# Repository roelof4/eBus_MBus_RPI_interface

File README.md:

# eBus_MBus_RPI_interface
Raspberry PI interface for eBus and M-Bus.

The interface combines a slave eBus interface and a master Mbus interface. This combination
is often present in heating systems such as gas boilers and heatpumps. For example, Vaillant
uses eBus to read and control.
The Mbus master is ideal to read heat meters, water meters and other sensors.
This interface provides power to the sensors and is thus classified as the master.
For safety purposes the eBus interface is fully galvanically shielded using optocouplers.

Both interfaces can be linked to serial (UART) ports on the Raspberry Pi. Version 4 and beyond
provide more than two UARTS and the user can select which one is used for either interface.
Older Raspberries can typically only use one UART. For these case the user can use serial to usb
cables using a separate 4-pin connector. Two are provided such that in principle the board
can be used standalone provided a 5V powersupply is present. When mounted as a HAT on the
Raspberry the 5V supply provided through the GPIO connector is used.

The interface also features a ONE WIRE sensor screw terminal which can act as a multiple temperature
sensor input (or whatever other ONE WIRE device available).

Note: the I2C EEPROM is optional and used for a system with automatic recognition.

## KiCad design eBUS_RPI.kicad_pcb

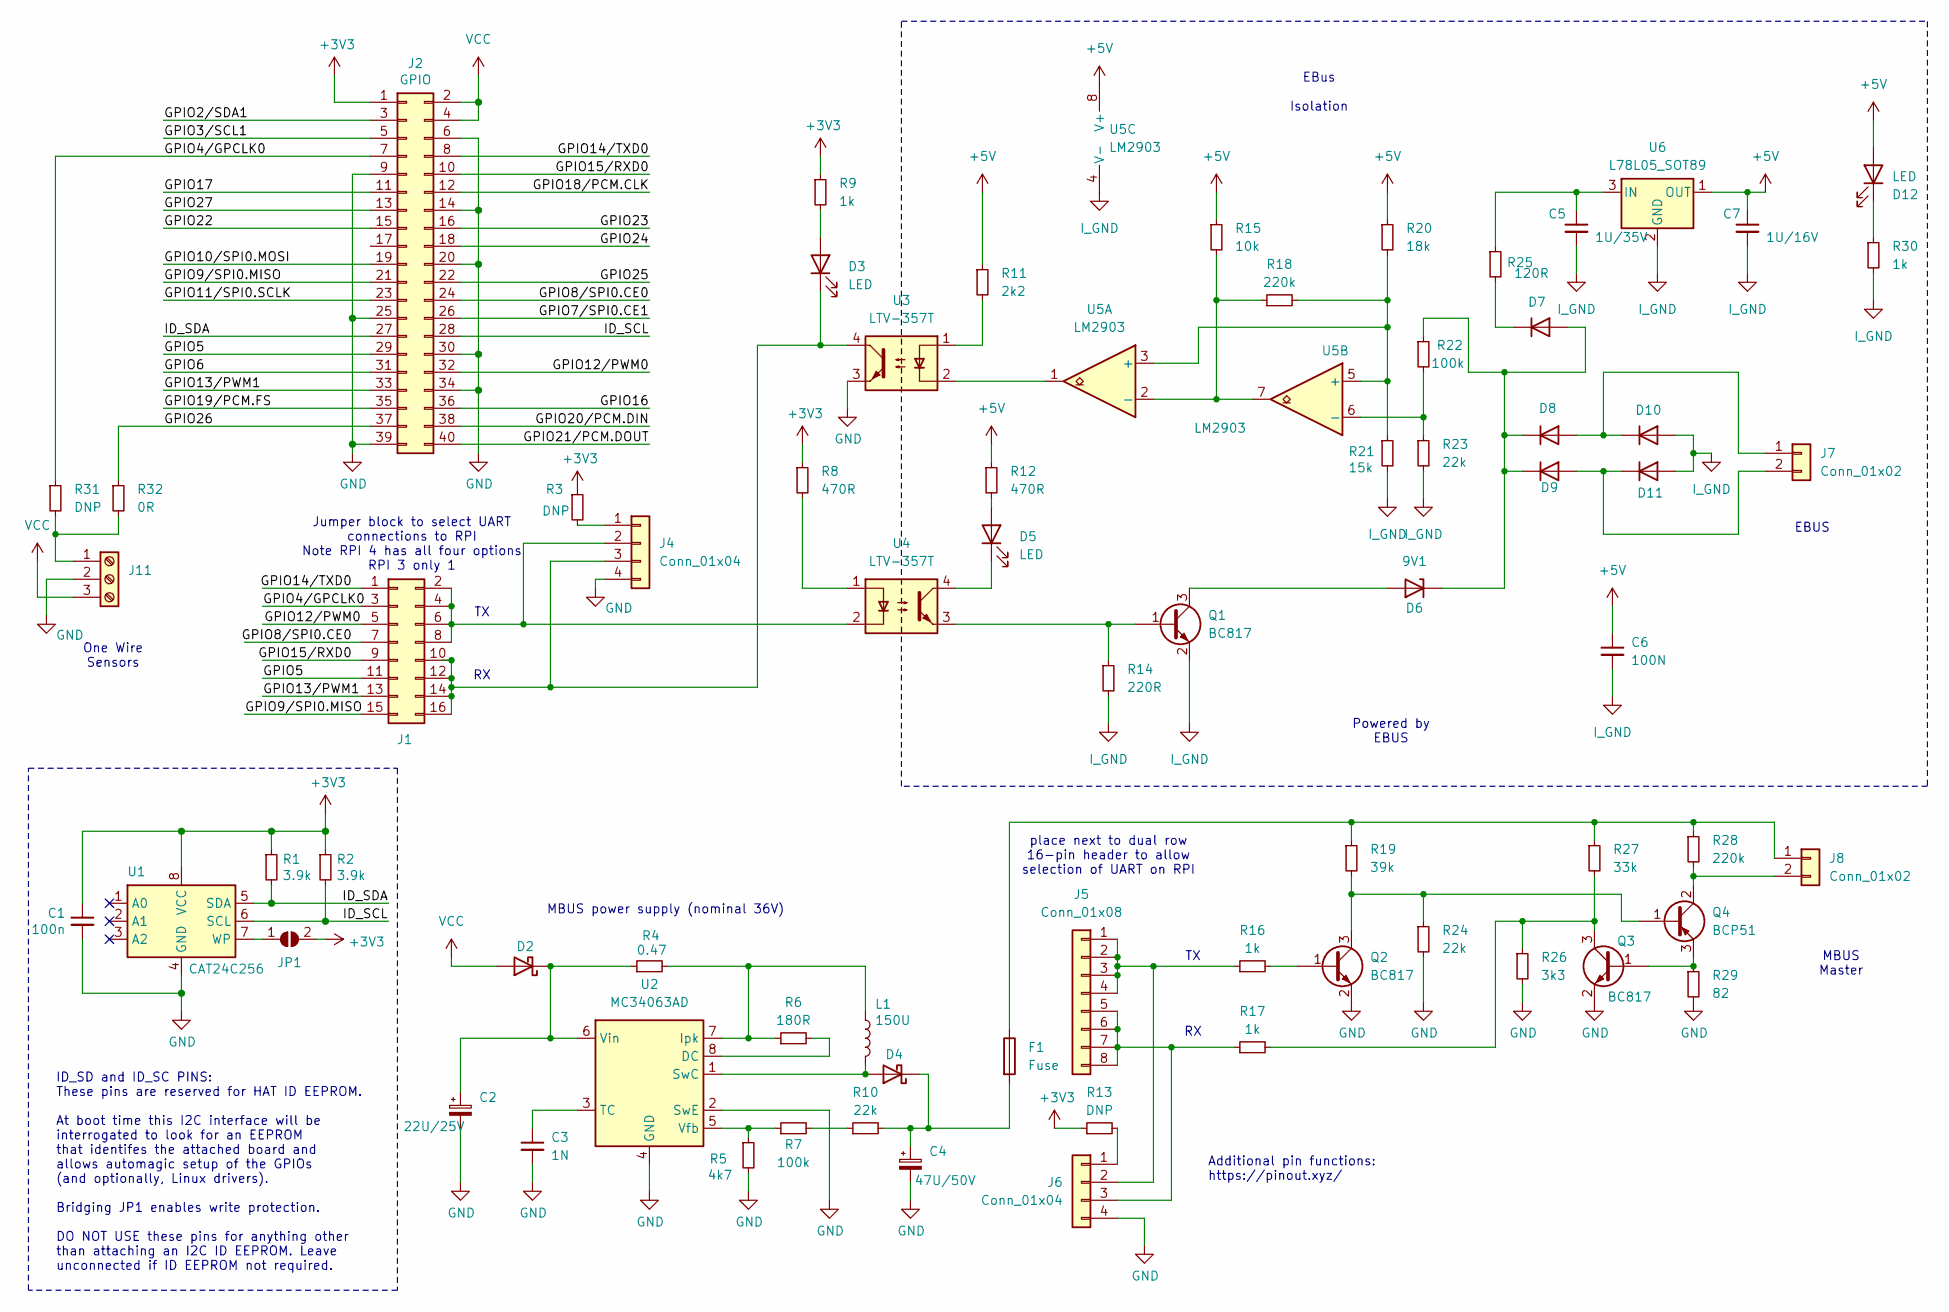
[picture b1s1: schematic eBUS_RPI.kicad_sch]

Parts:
C1: 100n; R_0603_1608Metric
C2: 22U/25V; CP_Elec_5x3.9
C3: 1N; C_0603_1608Metric
C4: 47U/50V; CP_Elec_5x5.7
C5: 1U/35V; C_0603_1608Metric
C6: 100N; C_0603_1608Metric
C7: 1U/16V; C_0603_1608Metric
D2, D4: D_Schottky; D_SMA
D3, D5, D12: LED; LED_0805_2012Metric
D6: 9V1; D_SMC
D7, D8, D9, D10, D11: BAS16W; SOT-323_SC-70
F1: Fuse; Fuse_2920_7451Metric
J1: Conn_02x08_Odd_Even; PinHeader_2x08_P2.54mm_Vertical
J2: GPIO; PinSocket_2x20_P2.54mm_Vertical
J4, J6: Conn_01x04; PinHeader_1x04_P2.54mm_Vertical
J5: Conn_01x08; PinHeader_1x08_P2.54mm_Vertical
J7, J8: Conn_01x02; PhoenixContact_MSTBA_2,5_2-G-5,08_1x02_P5.08mm_Horizontal
J11: Screw_Terminal_01x03; TerminalBlock_Phoenix_PT-1,5-3-5.0-H_1x03_P5.00mm_Horizontal
JP1: ID_WP; SolderJumper-2_P1.3mm_Open_TrianglePad1.0x1.5mm
L1: 150U; L_7.3x7.3_H4.5
Q1, Q2, Q3: BC817; SOT-23
Q4: BCP51; SOT-223-3_TabPin2
R1, R2: 3.9k; R_0603_1608Metric
R3, R13, R31: DNP; R_0603_1608Metric
R4: 0.47; R_0603_1608Metric
R5: 4k7; R_0603_1608Metric
R6: 180R; R_0603_1608Metric
R7, R22: 100k; R_0603_1608Metric
R8, R12: 470R; R_0603_1608Metric
R9, R16, R17, R30: 1k; R_0603_1608Metric
R10, R23, R24: 22k; R_0603_1608Metric
R11: 2k2; R_0603_1608Metric
R14: 220R; R_0603_1608Metric
R15: 10k; R_0603_1608Metric
R18, R28: 220k; R_0603_1608Metric
R19: 39k; R_0603_1608Metric
R20: 18k; R_0603_1608Metric
R21: 15k; R_0603_1608Metric
R25: 120R; R_0603_1608Metric
R26: 3k3; R_0603_1608Metric
R27: 33k; R_0603_1608Metric
R29: 82; R_0603_1608Metric
R32: 0R; R_0603_1608Metric
U1: CAT24C256; SOIC-8_3.9x4.9mm_P1.27mm
U2: MC34063AD; SOIC-8_3.9x4.9mm_P1.27mm
U3, U4: LTV-357T; SO-4_4.4x3.6mm_P2.54mm
U5: LM2903; SOIC-8_3.9x4.9mm_P1.27mm
U6: L78L05_SOT89; SOT-89-3

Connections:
+3V3: C1.1, J2.1, JP1.2 (B), R1.1, R2.1, R3.1, R8.1, R9.1, R13.1, U1.8 (VCC)
+5V: C6.1, C7.1, D12.2 (A), R11.1, R12.1, R15.1, R20.1, U5.8 (V+), U6.1 (OUT)
/GPIO2/SDA1: J2.3
/GPIO3/SCL1: J2.5
/GPIO4/GPCLK0: J1.3, J2.7, R31.1
/GPIO5: J1.11, J2.29
/GPIO6: J2.31
/GPIO7/SPI0.CE1: J2.26
/GPIO8/SPI0.CE0: J1.7, J2.24
/GPIO9/SPI0.MISO: J1.15, J2.21
/GPIO10/SPI0.MOSI: J2.19
/GPIO11/SPI0.SCLK: J2.23
/GPIO12/PWM0: J1.5, J2.32
/GPIO13/PWM1: J1.13, J2.33
/GPIO14/TXD0: J1.1, J2.8
/GPIO15/RXD0: J1.9, J2.10
/GPIO16: J2.36
/GPIO17: J2.11
/GPIO18/PCM.CLK: J2.12
/GPIO19/PCM.FS: J2.35
/GPIO20/PCM.DIN: J2.38
/GPIO21/PCM.DOUT: J2.40
/GPIO22: J2.15
/GPIO23: J2.16
/GPIO24: J2.18
/GPIO25: J2.22
/GPIO26: J2.37, R32.1
/GPIO27: J2.13
/ID_SCL: J2.28, R2.2, U1.6 (SCL)
/ID_SDA: J2.27, R1.2, U1.5 (SDA)
GND: C1.2, C2.2, C3.2, C4.2, J2.6, J2.9, J2.14, J2.20, J2.25, J2.30, J2.34, J2.39, J4.4, J6.4, J11.2, Q2.2 (E), Q3.2 (E), R5.2, R24.2, R26.2, R29.2, U1.4 (GND), U2.2 (SwE), U2.4 (GND), U3.3
I_GND: C5.2, C6.2, C7.2, D10.1 (A), D11.1 (A), Q1.2 (E), R14.2, R21.2, R23.2, R30.2, U5.4 (V-), U6.2 (GND)
unnamed: C2.1, D2.1 (K), R4.1, U2.6 (Vin)
unnamed: D3.2 (A), R9.2
unnamed: D3.1 (K), J1.10, J1.12, J1.14, J1.16, J4.3, U3.4
unnamed: D4.2 (A), L1.2, U2.1 (SwC)
unnamed: C4.1, D4.1 (K), F1.2, R10.2
unnamed: D5.2 (A), R12.2
unnamed: D5.1 (K), U4.4
unnamed: D6.2 (A), Q1.3 (C)
unnamed: D6.1 (K), D7.1 (A), D8.3 (K), D9.3 (K), R22.1
unnamed: D7.3 (K), R25.2
unnamed: D8.1 (A), D10.3 (K), J7.1
unnamed: D9.1 (A), D11.3 (K), J7.2
unnamed: D12.1 (K), R30.1
unnamed: J1.2, J1.4, J1.6, J1.8, J4.2, U4.2
unnamed: J4.1, R3.2
unnamed: J5.1, J5.2, J5.3, J5.4, J6.2, R16.1
unnamed: J5.5, J5.6, J5.7, J5.8, J6.3, R17.1
unnamed: J6.1, R13.2
unnamed: F1.1, J8.1, R19.1, R27.1, R28.1
unnamed: J8.2, Q4.2 (C), R28.2
unnamed: J11.1, R31.2, R32.2
unnamed: JP1.1 (A), U1.7 (WP)
unnamed: Q1.1 (B), R14.1, U4.3
unnamed: Q2.1 (B), R16.2
unnamed: Q2.3 (C), Q4.1 (B), R19.2, R24.1
unnamed: Q3.1 (B), Q4.3 (E), R29.1
unnamed: Q3.3 (C), R17.2, R26.1, R27.2
unnamed: R8.2, U4.1
unnamed: R7.2, R10.1
unnamed: R11.2, U3.1
unnamed: R6.2, U2.8 (DC)
unnamed: L1.1, R4.2, R6.1, U2.7 (Ipk)
unnamed: C3.1, U2.3 (TC)
unnamed: R5.1, R7.1, U2.5 (Vfb)
unnamed: U3.2, U5.1
unnamed: R18.2, R20.2, R21.1, U5.3 (+), U5.5 (+)
unnamed: R15.2, R18.1, U5.2 (-), U5.7
unnamed: R22.2, R23.1, U5.6 (-)
unnamed: C5.1, R25.1, U6.3 (IN)
VCC: D2.2 (A), J2.2, J2.4, J11.3

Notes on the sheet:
Powered by EBUS
One Wire Sensors
MBUS Master
EBUS
place next to dual row 16-pin header to allow selection of UART on RPI
ID_SD and ID_SC PINS: These pins are reserved for HAT ID EEPROM. At boot time this I2C interface will be interrogated to look for an EEPROM that identifes the attached board and allows automagic setup of the GPIOs (and optionally, Linux drivers). Bridging JP1 enables write protection. DO NOT USE th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
MBUS power supply (nominal 36V)
EBus Isolation
Additional pin functions: https://pinout.xyz/
Jumper block to select UART connections to RPI Note RPI 4 has all four options RPI 3 only 1

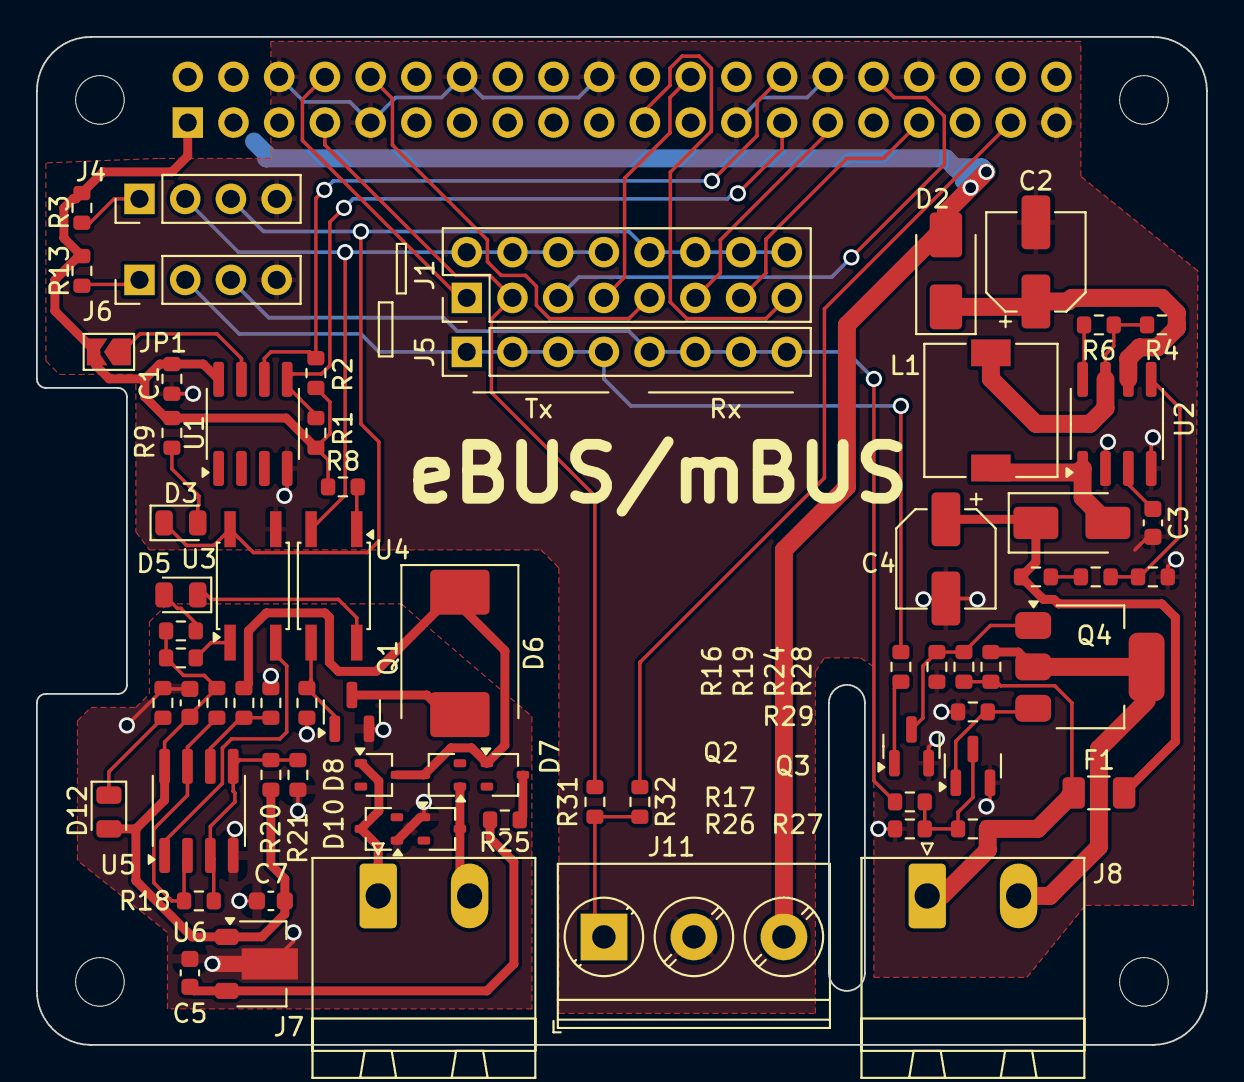
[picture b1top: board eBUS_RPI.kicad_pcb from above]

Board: 2 copper layers, 65.0 x 56.0 mm, 75 parts (1 on the bottom side), 55 nets.

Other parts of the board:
MH1, MH2, MH3, MH4: MountingHole_2.7mm_M2.5

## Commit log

2024-03-19 commit KiCad files
2024-03-19 revised readme file
2024-03-19 take out production files
2024-03-20 small change
